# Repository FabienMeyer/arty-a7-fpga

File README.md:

# Project Brief: Smart 3S Li-ion UPS & Fan Controller (Dual-Zone Sensing)

## 1. System Overview

Design a professional-grade Arduino-based Fan Controller and Power Management system for a custom PCB. The device manages three high-end 12V PWM fans and features a full battery backup (UPS) system.

**Physical Configuration:**

- **Control Box (3D Printed):** Houses the Arduino Nano, 16x2 LCD, PEC11 Encoder, Battery Pack, and an **Internal Safety Temperature Sensor**.

- **Fan Housing (Wood):** Houses 3x 12V PWM fans and a **Deported Environmental Sensor** (Temperature, Humidity, Pressure) for ambient weather data.

---

## 2. Power Architecture Requirements

- **Dual-Input Power Path:** - Primary: 15V DC Wall Adapter.

    - Backup: 3S Li-ion Battery Pack (Nominal 11.1V, Max 12.6V).

- **Load Sharing:** Run fans/logic and charge the battery simultaneously. Seamless switching to battery when unplugged.

- **Logic Rail:** High-efficiency Step-Down (Buck) regulation to 5V for logic components.

- **Battery Monitoring:** I2C-based sensing for real-time Voltage, Current (mA), and Power (Watts).

- **Capacity Assumption:** 6000mAh (3S2P configuration).

---

## 3. Safety & Protection Requirements

- **Thermal Safety:** Monitor the **Internal Control Box Temperature**. If the internal electronics/battery compartment exceeds a safe threshold (e.g., 55°C), trigger an alert or shutdown.

- **Hardware Protection:** Implementation of a 3S BMS (Battery Management System).

- **Software-Controlled Safety Switch:** High-Side Load MOSFET controlled by Arduino (Pin D6) to disconnect power if:

    - Critical Undervoltage (<9.6V).

    - Overcurrent/Short-circuit (>2A).

    - Critical Internal Overheat.

---

## 4. Actuators & Interface

- **Fan Control:** 3x Fans on **Pin D9**. 25kHz Ultrasonic PWM (Timer 1) for silent operation.

- **User Interface:**

    - **Input:** PEC11 Rotary Encoder with push-button (D2/D3/D5).

    - **Display:** 16x2 LCD via I2C.

- **Dual-Zone I2C Sensors:**

    - **Sensor A (Internal):** Temperature only (for box safety).

    - **Sensor B (Remote):** Temperature, Humidity, Pressure (Deported to the wooden fan housing).

- **Power Saving (Night Mode):**

    - LCD backlight controlled via MOSFET on **Pin D4**.

    - 30-second inactivity timeout; wake on encoder interaction.

---

## 5. Software Logic (State Machine)

- **Navigation:** Rotate encoder to scroll through pages:

    1. **Weather (Remote):** Ambient Temp, Humidity, Pressure.

    2. **System Health (Internal):** Box Temp, Battery Voltage, Current Draw, and "Time Remaining."

    3. **Fan Pages (1-3):** Individual speed and status for each fan.

- **Interaction:** Short Press to Edit Speed (0-100%); Long Press (1s) to Toggle Fan ON/OFF.

- **Fault Handling:** If a fault (Overheat/Overcurrent/Low-V) is detected, pull D6 LOW and display specific error.

---

## 6. Requested Deliverables

1. **Component Proposals:** Specific high-efficiency parts for the 3S Charger, Power Path, Current Sensor, Buck Regulator, and MOSFETs.

2. **Dual-Sensor Strategy:** Propose the best I2C sensors to avoid address conflicts (e.g., using different addresses or an I2C multiplexer).

3. **Firmware:** Complete, non-blocking Arduino C++ code (`.ino`) including 25kHz PWM and safety logic.

4. **Wiring/PCB Guidance:** Advice on routing the deported I2C sensor to the wooden box over a distance while maintaining signal integrity (pull-up resistor placement).

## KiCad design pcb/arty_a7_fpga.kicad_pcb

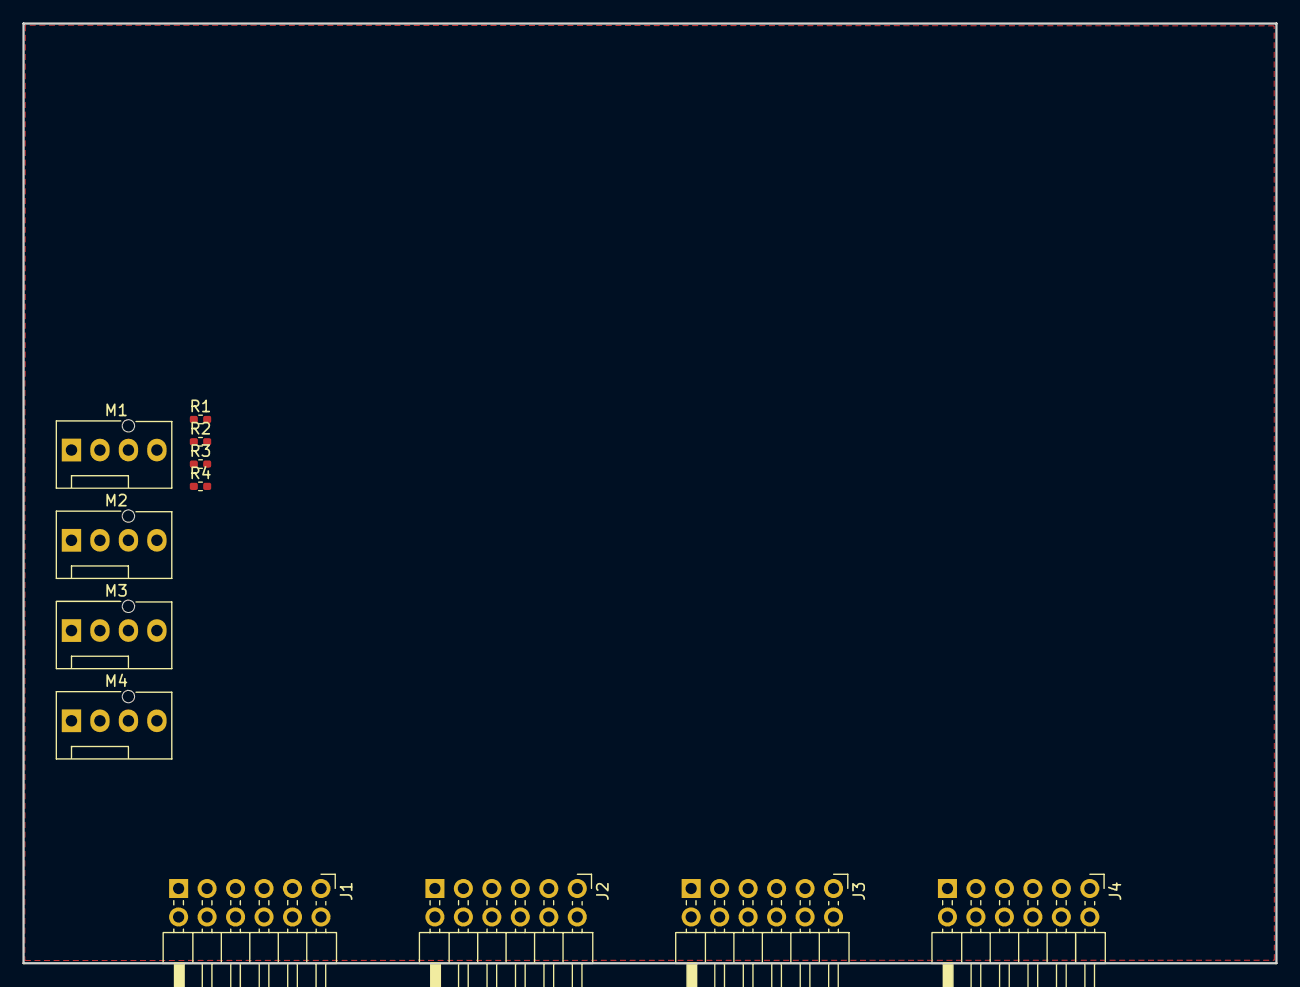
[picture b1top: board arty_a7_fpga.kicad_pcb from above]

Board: 2 copper layers, 111.8 x 83.8 mm, 12 parts (0 on the bottom side), 11 nets, no tracks yet.

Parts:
J1, J2, J3, J4: PmodHeader_2x06; PmodHeader_2x06_P2.54mm_Horizontal
M1, M2, M3, M4: Fan_4pin; FanPinHeader_1x04_P2.54mm_Vertical
R1, R2, R3, R4: 100K; R_0402_1005Metric_Pad0.72x0.64mm_HandSolder

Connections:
+3.3V: J1.6, J1.12, J2.6, J2.12, J3.6, J3.12, J4.6, J4.12, R1.1, R2.1, R3.1, R4.1
+12V: M1.2 (+), M2.2 (+), M3.2 (+), M4.2 (+)
/M1_PWM: J1.3, M1.4 (PWM)
/M1_TACHO: J1.4, M1.3 (Tacho), R1.2
/M2_PWM: J1.1, M2.4 (PWM)
/M2_TACHO: J1.2, M2.3 (Tacho), R2.2
/M3_PWM: J1.9, M3.4 (PWM)
/M3_TACHO: J1.10, M3.3 (Tacho), R3.2
/M4_PWM: J1.7, M4.4 (PWM)
/M4_TACHO: J1.8, M4.3 (Tacho), R4.2
GND: J1.5, J1.11, J2.5, J2.11, J3.5, J3.11, J4.5, J4.11, M1.1 (-), M2.1 (-), M3.1 (-), M4.1 (-)

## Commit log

2026-03-24 feature: initial architecture
